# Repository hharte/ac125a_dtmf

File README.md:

# OKI AC125A Crossbar PBX DTMF Adapter

The OKI AC125A Crossbar PBX has provision for dual DTMF converters connected to 50-pin telco connector #6.  This project consists of a carrier board containing two [WE 755A PBX DTMF Converter](https://github.com/hharte/we755a_dtmf) boards.  This adapter plugs directly into connector #6.

# Current Status

The Issue 3 board is being fabbed.  Operational status is not yet known.

The Issue 2 board has been brought up and is in operation on the PBX, available via [C*NET](https://www.ckts.info/) at 1-558-2500 and on [NPSTN](http://www.npstn.us/) at 558-2500.

## Bill of Materials

[Interactive BOM](https://html-preview.github.io/?url=https://github.com/hharte/ac125a_dtmf/blob/main/hardware/bom/ibom.html)

# Installation

Just plug the AC125A DTMF converter into 50-pin connector J6 of the PBX.

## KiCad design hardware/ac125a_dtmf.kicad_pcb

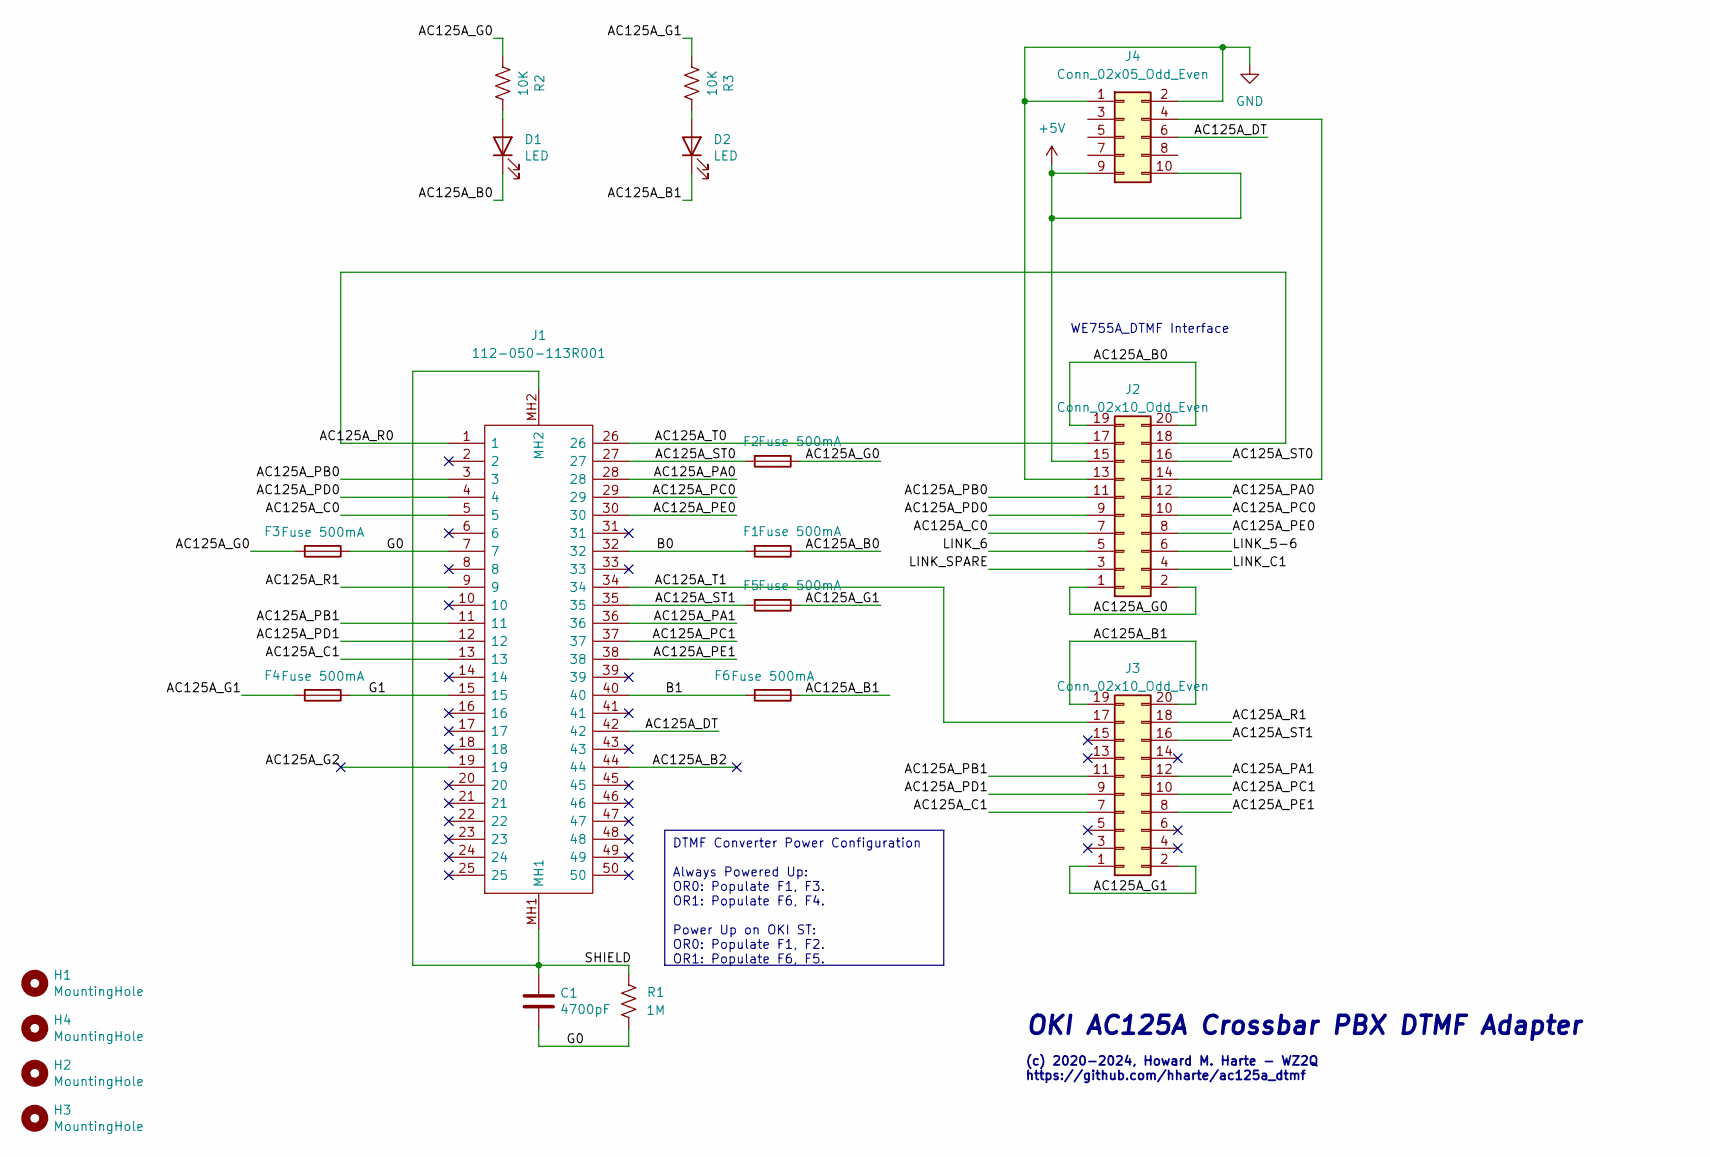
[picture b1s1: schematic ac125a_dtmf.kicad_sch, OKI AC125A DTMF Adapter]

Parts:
C1: 4700pF; C_Disc_D4.3mm_W1.9mm_P5.00mm; MPN S472M39Z5UN63J5R; Digi-Key_PN 1288PH-ND
D1, D2: LED; LED_D5.0mm; MPN XLUR12D; Digi-Key_PN 1497-1031-ND
F1, F2, F3, F4, F5, F6: Fuse 500mA; R_Axial_DIN0207_L6.3mm_D2.5mm_P10.16mm_Horizontal; MPN 0251.500MXL; Digi-Key_PN F2311-ND
H1, H2, H3, H4: MountingHole; MountingHole_2.7mm_Pad
J1: 112-050-113R001; 112050113R001; Mouser Part Number 636-112-050-113R001
J2, J3: Conn_02x10_Odd_Even; WE755A-DTMF; MPN SFH11-PBPC-D10-ST-BK; Digi-Key_PN S9197-ND
J4: Conn_02x05_Odd_Even; PinHeader_2x05_P2.54mm_Vertical; MPN SFH11-PBPC-D05-ST-BK; Digi-Key_PN S9194-ND
R1: 1M; R_Axial_DIN0207_L6.3mm_D2.5mm_P7.62mm_Horizontal; MPN CFM12JT1M00; Digi-Key_PN S1MHCT-ND
R2, R3: 10K; R_Axial_DIN0207_L6.3mm_D2.5mm_P7.62mm_Horizontal; MPN CFM12JT10K0; Digi-Key_PN S10KHCT-ND

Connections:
+5V: J2.15, J4.9, J4.10
/AC125A_B0: D1.1 (K), F1.1, J2.19, J2.20
/AC125A_B1: D2.1 (K), F6.1, J3.19, J3.20
/AC125A_B2: J1.44
/AC125A_C0: J1.5, J2.7
/AC125A_C1: J1.13, J3.7
/AC125A_DT: J1.42, J4.6
/AC125A_G0: F2.1, F3.2, J2.1, J2.2, R2.2
/AC125A_G1: F4.2, F5.1, J3.1, J3.2, R3.2
/AC125A_G2: J1.19
/AC125A_PA0: J1.28, J2.12
/AC125A_PA1: J1.36, J3.12
/AC125A_PB0: J1.3, J2.11
/AC125A_PB1: J1.11, J3.11
/AC125A_PC0: J1.29, J2.10
/AC125A_PC1: J1.37, J3.10
/AC125A_PD0: J1.4, J2.9
/AC125A_PD1: J1.12, J3.9
/AC125A_PE0: J1.30, J2.8
/AC125A_PE1: J1.38, J3.8
/AC125A_R0: J1.1, J2.18
/AC125A_R1: J1.9, J3.18
/AC125A_ST0: F2.2, J1.27, J2.16
/AC125A_ST1: F5.2, J1.35, J3.16
/AC125A_T0: J1.26, J2.17
/AC125A_T1: J1.34, J3.17
/B0: F1.2, J1.32
/B1: F6.2, J1.40
/G0: C1.2, F3.1, J1.7, R1.2
/G1: F4.1, J1.15
/LINK_5-6: J2.6
/LINK_6: J2.5
/LINK_C1: J2.4
/LINK_SPARE: J2.3
/SHIELD: C1.1, J1.MH1, J1.MH2, R1.1
GND: J2.13, J4.1, J4.2
unnamed: D1.2 (A), R2.1
unnamed: D2.2 (A), R3.1
unnamed: J2.14, J4.4

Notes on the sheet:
DTMF Converter Power Configuration Always Powered Up: OR0: Populate F1, F3. OR1: Populate F6, F4. Power Up on OKI ST: OR0: Populate F1, F2. OR1: Populate F6, F5.
OKI AC125A Crossbar PBX DTMF Adapter
WE755A_DTMF Interface
(c) 2020-2024, Howard M. Harte - WZ2Q https://github.com/hharte/ac125a_dtmf

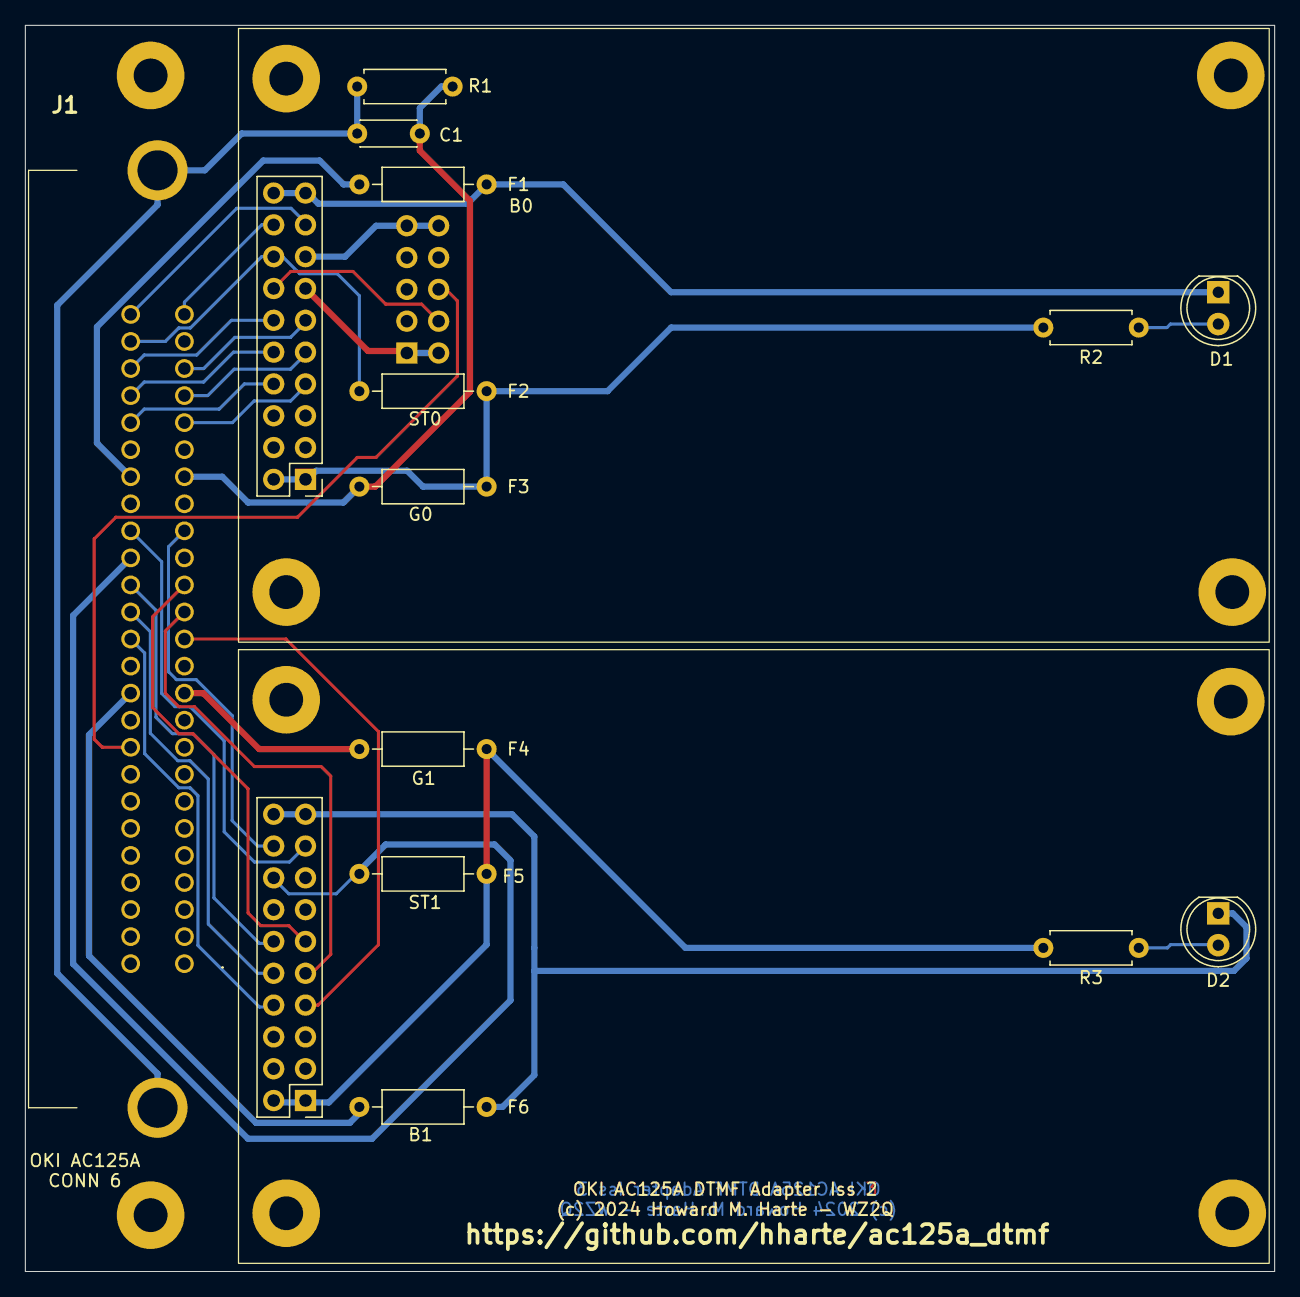
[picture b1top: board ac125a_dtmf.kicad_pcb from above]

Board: 2 copper layers, 99.8 x 99.5 mm, 20 parts (1 on the bottom side), 33 nets.

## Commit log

2020-05-24 Initial Issue 1 board bringup.
    This is not complete, but it is useful for testing
    the hardware.
2020-05-30 AC125A DTMF Converter Issue 1
    Schematic (pdf) and gerber files sent to pcbway.com
2020-05-31 Update schematic for Issue 2.
2020-06-20 Add event buffer to track OR operations.
2020-06-20 Update resistor values for DTMF decoders.
2020-06-27 Final schematic and PCB layout for Issue 2.
    Corrected errors in Issue 1 and fabbed out the PCB.
2020-07-05 Add photos of the Issue 2 PCB.
2022-08-07 Fix a couple DRC errors in the layout.
2024-04-14 Issue 3: Utilize we755a_dtmf boards.
    * Carrier for 2*we755a_dtmf boards.

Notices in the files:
hardware/ac125a_dtmf.kicad_pcb:
(c) 2024 Howard M. Harte - WZ2Q
